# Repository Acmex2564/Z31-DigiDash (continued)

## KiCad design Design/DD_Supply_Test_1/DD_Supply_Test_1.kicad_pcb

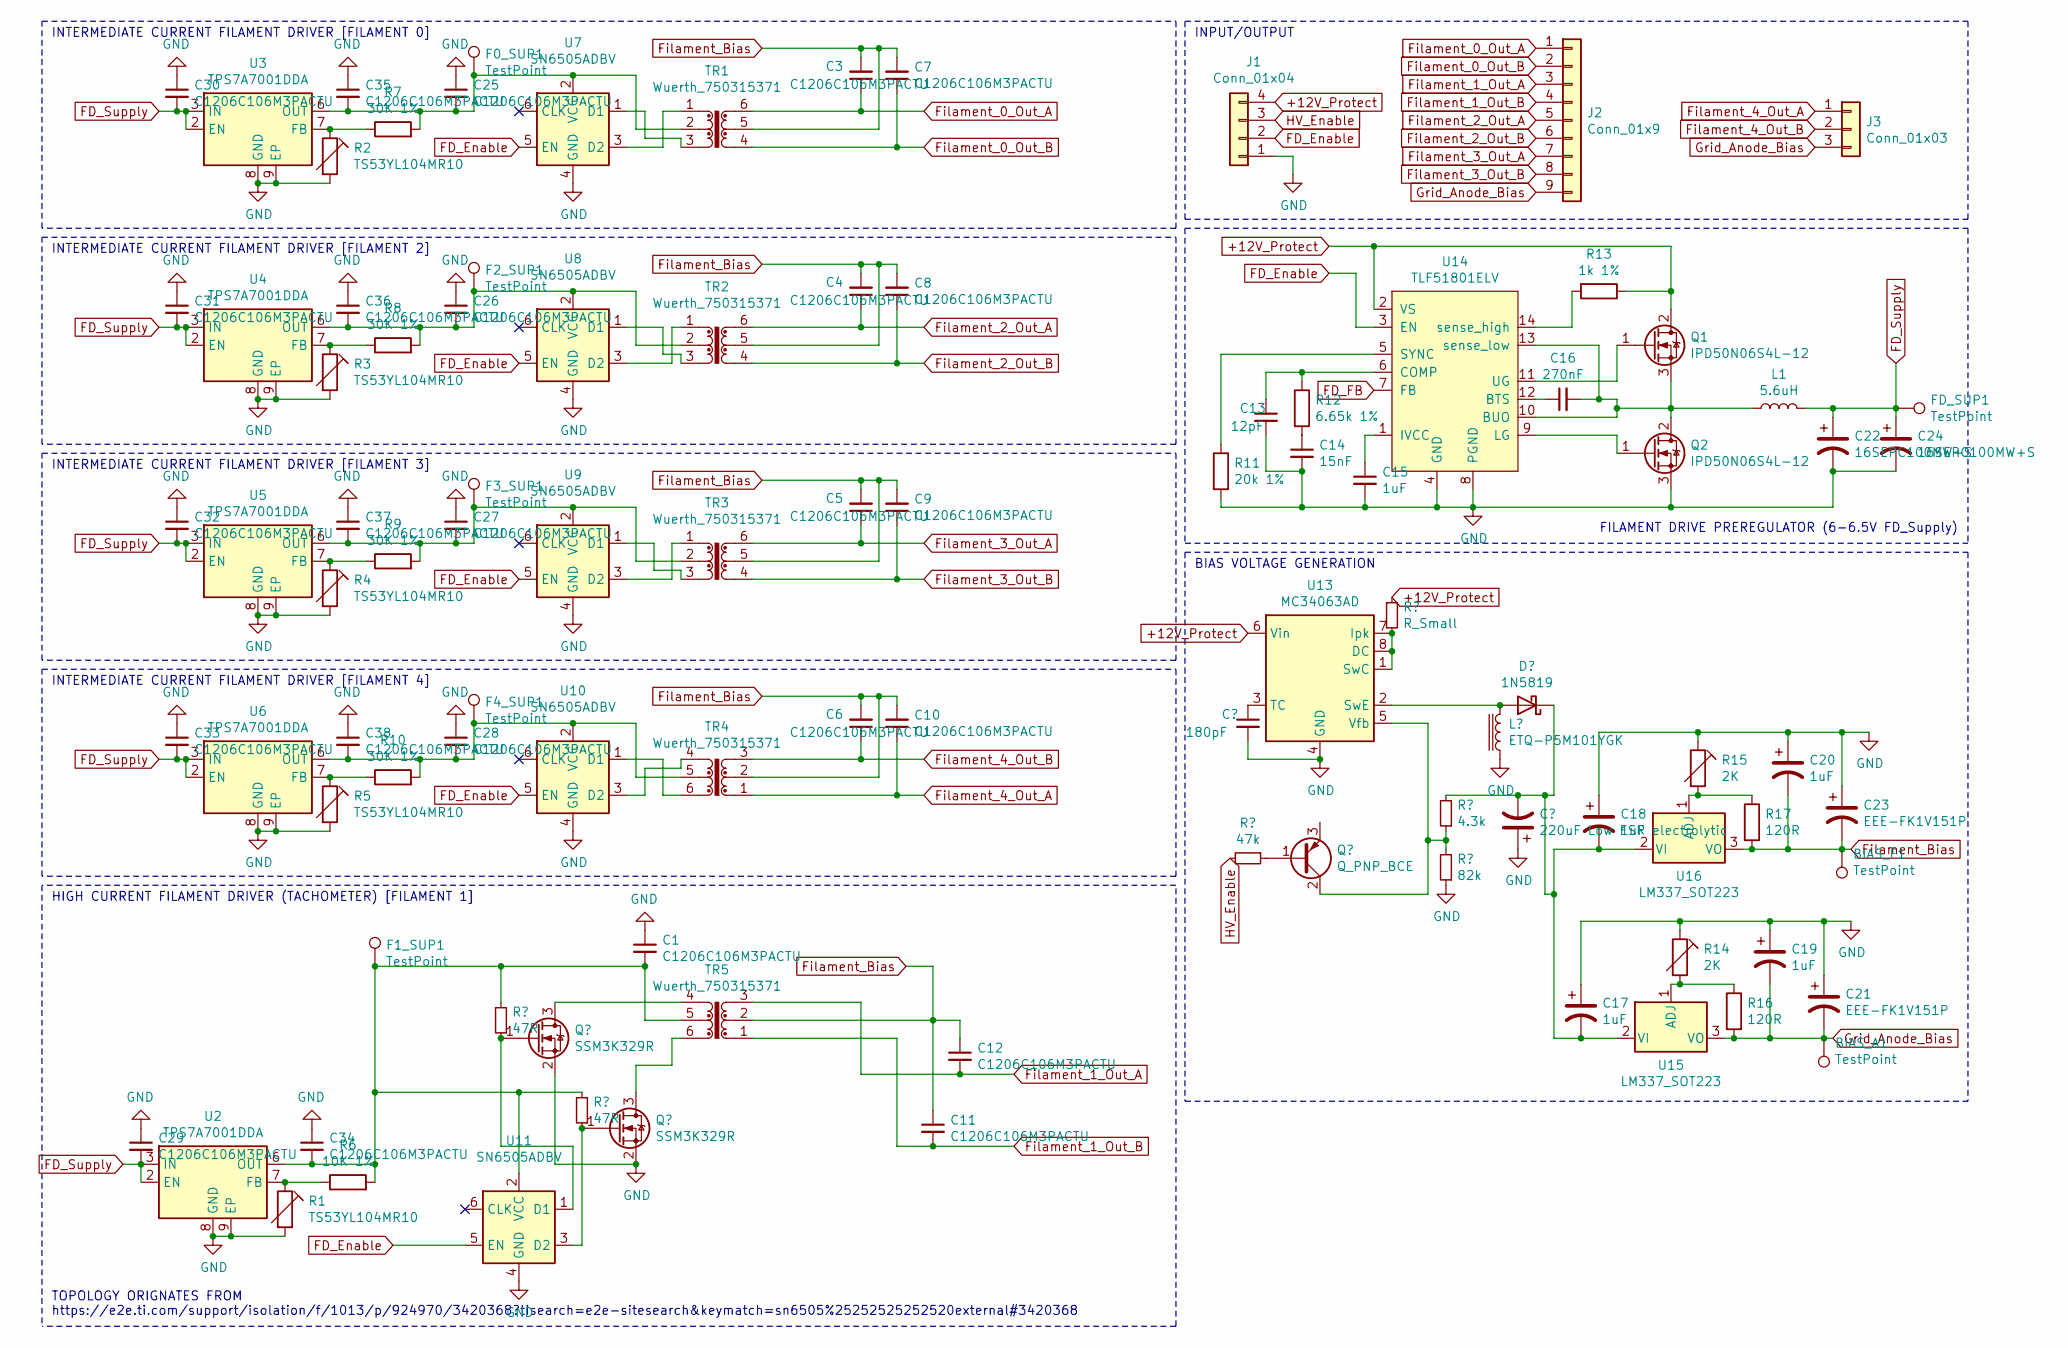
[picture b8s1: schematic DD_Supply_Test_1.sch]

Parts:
BIAS_A1: TestPoint; TestPoint_Pad_D2.0mm
BIAS_F1: TestPoint; TestPoint_Pad_D2.0mm
C1, C3, C4, C5, C6, C7, C8, C9, C10, C11, C12, C25, C26, C27, C28, C29, C30, C31, C32, C33, C34, C35, C36, C37, C38: C1206C106M3PACTU; C_1206_3216Metric_Pad1.33x1.80mm_HandSolder
C13: 12pF; C_1206_3216Metric_Pad1.33x1.80mm_HandSolder
C14: 15nF; C_1206_3216Metric_Pad1.33x1.80mm_HandSolder
C15: 1uF; C_1206_3216Metric_Pad1.33x1.80mm_HandSolder
C16: 270nF; C_1206_3216Metric_Pad1.33x1.80mm_HandSolder
C17, C18, C19, C20: 1uF; CP_EIA-7132-28_AVX-C_Pad2.72x3.50mm_HandSolder
C21, C23: EEE-FK1V151P; CP_Elec_8x10.5
C22, C24: 16SEPC100MW+S; CP_Radial_D6.3mm_P2.50mm
F0_SUP1, F1_SUP1, F2_SUP1, F3_SUP1, F4_SUP1: TestPoint; TestPoint_Pad_D2.0mm
FD_SUP1: TestPoint; TestPoint_Pad_D2.0mm
J1: Conn_01x04; PinHeader_1x04_P2.54mm_Vertical
J2: Conn_01x9; PinHeader_1x09_P2.54mm_Vertical
J3: Conn_01x03; PinHeader_1x03_P2.54mm_Vertical
L1: 5.6uH; L_12x12mm_H8mm
Q1, Q2: IPD50N06S4L-12; TO-252-2
R1, R2, R3, R4, R5: TS53YL104MR10; Potentiometer_Vishay_TS53YL_Vertical
R6: 10K 1%; R_1206_3216Metric_Pad1.30x1.75mm_HandSolder
R7, R8, R9, R10: 30K 1%; R_1206_3216Metric_Pad1.30x1.75mm_HandSolder
R11: 20k 1%; R_1206_3216Metric_Pad1.30x1.75mm_HandSolder
R12: 6.65k 1%; R_1206_3216Metric_Pad1.30x1.75mm_HandSolder
R13: 1k 1%; R_1206_3216Metric_Pad1.30x1.75mm_HandSolder
R14, R15: 2K; R_1206_3216Metric_Pad1.30x1.75mm_HandSolder
R16, R17: 120R; R_1206_3216Metric_Pad1.30x1.75mm_HandSolder
TR1, TR2, TR3, TR4, TR5: Wuerth_750315371; Transformer_Wuerth_750315371
U2, U3, U4, U5, U6: TPS7A7001DDA; TI_SO-PowerPAD-8
U7, U8, U9, U10, U11: SN6505ADBV; SOT-23-6
U13: MC34063AD; SOIC-8_3.9x4.9mm_P1.27mm
U14: TLF51801ELV; SSOP-14_5.3x6.2mm_P0.65mm
U15, U16: LM337_SOT223; SOT-223-3_TabPin2

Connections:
FD_Enable: J1.2, U7.5 (EN), U8.5 (EN), U9.5 (EN), U10.5 (EN), U11.5 (EN), U14.3 (EN); also elsewhere on the board
FD_FB: U14.7 (FB)
FD_Supply: C22.1, C24.1, C29.2, C30.2, C31.2, C32.2, C33.2, FD_SUP1.1, L1.2, U2.2 (EN), U2.3 (IN), U3.2 (EN), U3.3 (IN), U4.2 (EN), U4.3 (IN), U5.2 (EN), U5.3 (IN), U6.2 (EN), U6.3 (IN)
Filament_0_Out_A: C3.1, J2.1, TR1.6
Filament_0_Out_B: C7.1, J2.2, TR1.4
Filament_1_Out_A: C12.2, J2.3, TR5.3; also elsewhere on the board
Filament_1_Out_B: C11.2, J2.4, TR5.1; also elsewhere on the board
Filament_2_Out_A: C4.1, J2.5, TR2.6
Filament_2_Out_B: C8.1, J2.6, TR2.4
Filament_3_Out_A: C5.1, J2.7, TR3.6
Filament_3_Out_B: C9.1, J2.8, TR3.4
Filament_4_Out_A: C10.1, J3.1, TR4.1
Filament_4_Out_B: C6.1, J3.2, TR4.3
Filament_Bias: BIAS_F1.1, C3.2, C4.2, C5.2, C6.2, C7.2, C8.2, C9.2, C10.2, C11.1, C12.1, C20.2, C23.2, R17.2, TR1.5, TR2.5, TR3.5, TR4.2, TR5.2, U16.3 (VO); also elsewhere on the board
GND: C1.1, C13.2, C14.2, C15.2, C17.1, C18.1, C19.1, C20.1, C21.1, C22.2, C23.1, C24.2, C25.1, C26.1, C27.1, C28.1, C29.1, C30.1, C31.1, C32.1, C33.1, C34.1, C35.1, C36.1, C37.1, C38.1, J1.1, Q2.3 (S), R1.2, R2.2, R3.2, R4.2, R5.2, R11.2, R14.1, R15.1, U2.8 (GND), U2.9 (EP), U3.8 (GND), U3.9 (EP), U4.8 (GND), U4.9 (EP), U5.8 (GND), U5.9 (EP), U6.8 (GND), U6.9 (EP), U7.4 (GND), U8.4 (GND), U9.4 (GND), U10.4 (GND), U11.4 (GND), U13.4 (GND), U14.4 (GND), U14.8 (PGND); also elsewhere on the board
Grid_Anode_Bias: BIAS_A1.1, C19.2, C21.2, J2.9, J3.3, R16.2, U15.3 (VO)
HV_Enable: J1.3; also elsewhere on the board
unnamed 17: C1.2, C34.2, F1_SUP1.1, R6.2, TR5.5, U2.6 (OUT), U11.2 (VCC); also elsewhere on the board
unnamed: C13.1, R12.1, U14.6 (COMP)
unnamed: C14.1, R12.2
unnamed: C15.1, U14.1 (IVCC)
unnamed: C16.1, U14.12 (BTS)
unnamed: C16.2, L1.1, Q1.3 (S), Q2.2 (D), U14.10 (BUO), U14.13 (sense_low)
unnamed: C17.2, C18.2, U15.2 (VI), U16.2 (VI)
unnamed: C25.2, C35.2, F0_SUP1.1, R7.2, TR1.2, U3.6 (OUT), U7.2 (VCC)
unnamed: C26.2, C36.2, F2_SUP1.1, R8.2, TR2.2, U4.6 (OUT), U8.2 (VCC)
unnamed: C27.2, C37.2, F3_SUP1.1, R9.2, TR3.2, U5.6 (OUT), U9.2 (VCC)
unnamed: C28.2, C38.2, F4_SUP1.1, R10.2, TR4.5, U6.6 (OUT), U10.2 (VCC)
unnamed 28: U13.5 (Vfb); also elsewhere on the board
unnamed: Q1.1 (G), U14.11 (UG)
unnamed: Q2.1 (G), U14.9 (LG)
unnamed: R1.1, R6.1, U2.7 (FB)
unnamed: R2.1, R7.1, U3.7 (FB)
unnamed: R3.1, R8.1, U4.7 (FB)
unnamed: R4.1, R9.1, U5.7 (FB)
unnamed: R5.1, R10.1, U6.7 (FB)
unnamed: R11.1, U14.5 (SYNC)
unnamed: R13.2, U14.14 (sense_high)
unnamed: R14.2, R16.1, U15.1 (ADJ)
unnamed: R15.2, R17.1, U16.1 (ADJ)
unnamed: TR1.1, U7.3 (D2)
unnamed: TR1.3, U7.1 (D1)
unnamed: TR2.1, U8.3 (D2)
unnamed: TR2.3, U8.1 (D1)
unnamed: TR3.1, U9.3 (D2)
unnamed: TR3.3, U9.1 (D1)
unnamed: TR4.4, U10.3 (D2)
unnamed: TR4.6, U10.1 (D1)
unnamed: TR5.4, U11.3 (D2)
unnamed: TR5.6, U11.1 (D1)
unnamed 79: U11.6 (CLK); also elsewhere on the board

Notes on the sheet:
HIGH CURRENT FILAMENT DRIVER (TACHOMETER) [FILAMENT 1]
INPUT/OUTPUT
INTERMEDIATE CURRENT FILAMENT DRIVER [FILAMENT 4]
INTERMEDIATE CURRENT FILAMENT DRIVER [FILAMENT 3]
INTERMEDIATE CURRENT FILAMENT DRIVER [FILAMENT 2]
INTERMEDIATE CURRENT FILAMENT DRIVER [FILAMENT 0]
BIAS VOLTAGE GENERATION
FILAMENT DRIVE PREREGULATOR (6-6.5V FD_Supply)
TOPOLOGY ORIGNATES FROM https://e2e.ti.com/support/isolation/f/1013/p/924970/3420368?tisearch=e2e-sitesearch&keymatch=sn6505%25252525252520external#3420368

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
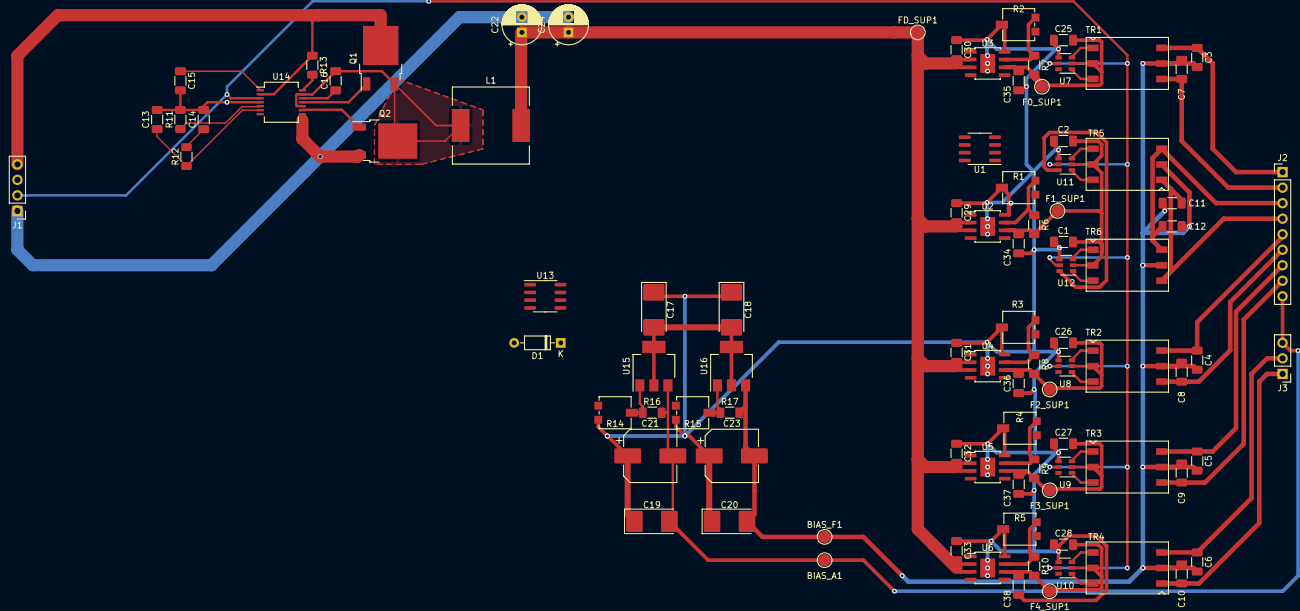
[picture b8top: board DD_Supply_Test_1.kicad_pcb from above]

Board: 2 copper layers, 92 parts (0 on the bottom side), 53 nets.

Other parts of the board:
C2: C1206C106M3PACTU; C_1206_3216Metric_Pad1.33x1.80mm_HandSolder
D1: 1N4148; D_DO-35_SOD27_P7.62mm_Horizontal
TR6: Wuerth_750315371; Transformer_Wuerth_750315371
U1: LM555xM; SOIC-8_3.9x4.9mm_P1.27mm
U12: SN6505ADBV; SOT-23-6

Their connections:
FD_Enable: U12.5; also elsewhere on the board
Filament_1_Out_A: TR6.6; also elsewhere on the board
Filament_1_Out_B: TR6.4; also elsewhere on the board
Filament_Bias: TR6.5; also elsewhere on the board
GND: C2.1, U12.4; also elsewhere on the board
HV_Enable: D1.2; also elsewhere on the board
unnamed 17: C2.2, TR6.2, U12.2; also elsewhere on the board
unnamed 28: D1.1; also elsewhere on the board
unnamed: TR6.1, U12.3
unnamed: TR6.3, U12.1
unnamed 79: U12.6; also elsewhere on the board

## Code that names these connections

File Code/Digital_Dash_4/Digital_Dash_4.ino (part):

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
// Pin definitions:
// Shift Register Enables
#define IC30_OE 16
#define IC31_OE 18
#define Main_OE 17
#define Satellite_OE 19

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#define PWR_ANALOG_EN 8

// SPI bus information
#define SPI1_LH 2
#define SPI1_SCK 32
#define SPI1_MISO 1
#define SPI1_MOSI 0

#define CS_BTN 15 //1x 74HC165D
#define CS_DISP_FUEL 3
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#define CS_DISP_OIL 9
#define CS_DISP_FUEL2 6

#define SPI2_LH 11
#define SPI2_SCK 46
#define SPI2_MISO 45
#define SPI2_MOSI 44

#define CS_ADC 43 //MCP3008
#define CS_DDC 35 //3x 74HC165D
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#define CS_TACHV 26 // tach load?

// Other outputs
#define ILLUM_DATA  33 //neopixels
#define ODO_PULSE 37
#define SPEED_PULSE 36
#define BLANK_CONTROL 5

//CANbus
#define CAN_INH 31
#define CAN_RX 30
#define CAN_TX 29

//Other inputs (freq and analog [on-board temp])
#define SPEED_IN 22
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
  //configure all I/O pins & set to known state
  Serial.print("Pin Config...");
  pinMode(IC30_OE, OUTPUT);
  pinMode(IC31_OE, OUTPUT);
  pinMode(Main_OE, OUTPUT);
  pinMode(Satellite_OE, OUTPUT);

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  digitalWrite(PWR_ANALOG_EN, LOW);


  pinMode(SPI1_LH, OUTPUT);
  pinMode(SPI1_SCK, OUTPUT);
  pinMode(SPI1_MOSI, OUTPUT);
  pinMode(SPI1_MISO, INPUT);
  pinMode(SPI2_LH, OUTPUT);
  pinMode(SPI2_SCK, OUTPUT);
  pinMode(SPI2_MOSI, OUTPUT);
  pinMode(SPI2_MISO, INPUT);


  pinMode(CS_BTN, OUTPUT);
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  digitalWrite(CS_SPEEDH, HIGH);


  pinMode(ILLUM_DATA, OUTPUT);
  pinMode(ODO_PULSE, OUTPUT);
  pinMode(SPEED_PULSE, OUTPUT);
  pinMode(BLANK_CONTROL, OUTPUT);
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  pinMode(FUEL_IN, INPUT);
  pinMode(BOARD_TEMP, INPUT);

  pinMode(CAN_INH, OUTPUT);
  digitalWrite(CAN_INH, HIGH);

  pinMode(ODO_DATA, OUTPUT);
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
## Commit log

2021-01-05 Rename Images.md to README.md
2022-04-08 Add & commit board designs
2022-04-08 Add demo code
2022-09-29 Catchup Commit
2022-12-19 Split descriptions to early/late
2022-12-19 Re-add early descriptions
2025-03-21 Catchup commit.
2025-03-21 Update README.md to reflect current state.
2025-04-20 warning module update; ws2812->ws2813 (backup data in)
